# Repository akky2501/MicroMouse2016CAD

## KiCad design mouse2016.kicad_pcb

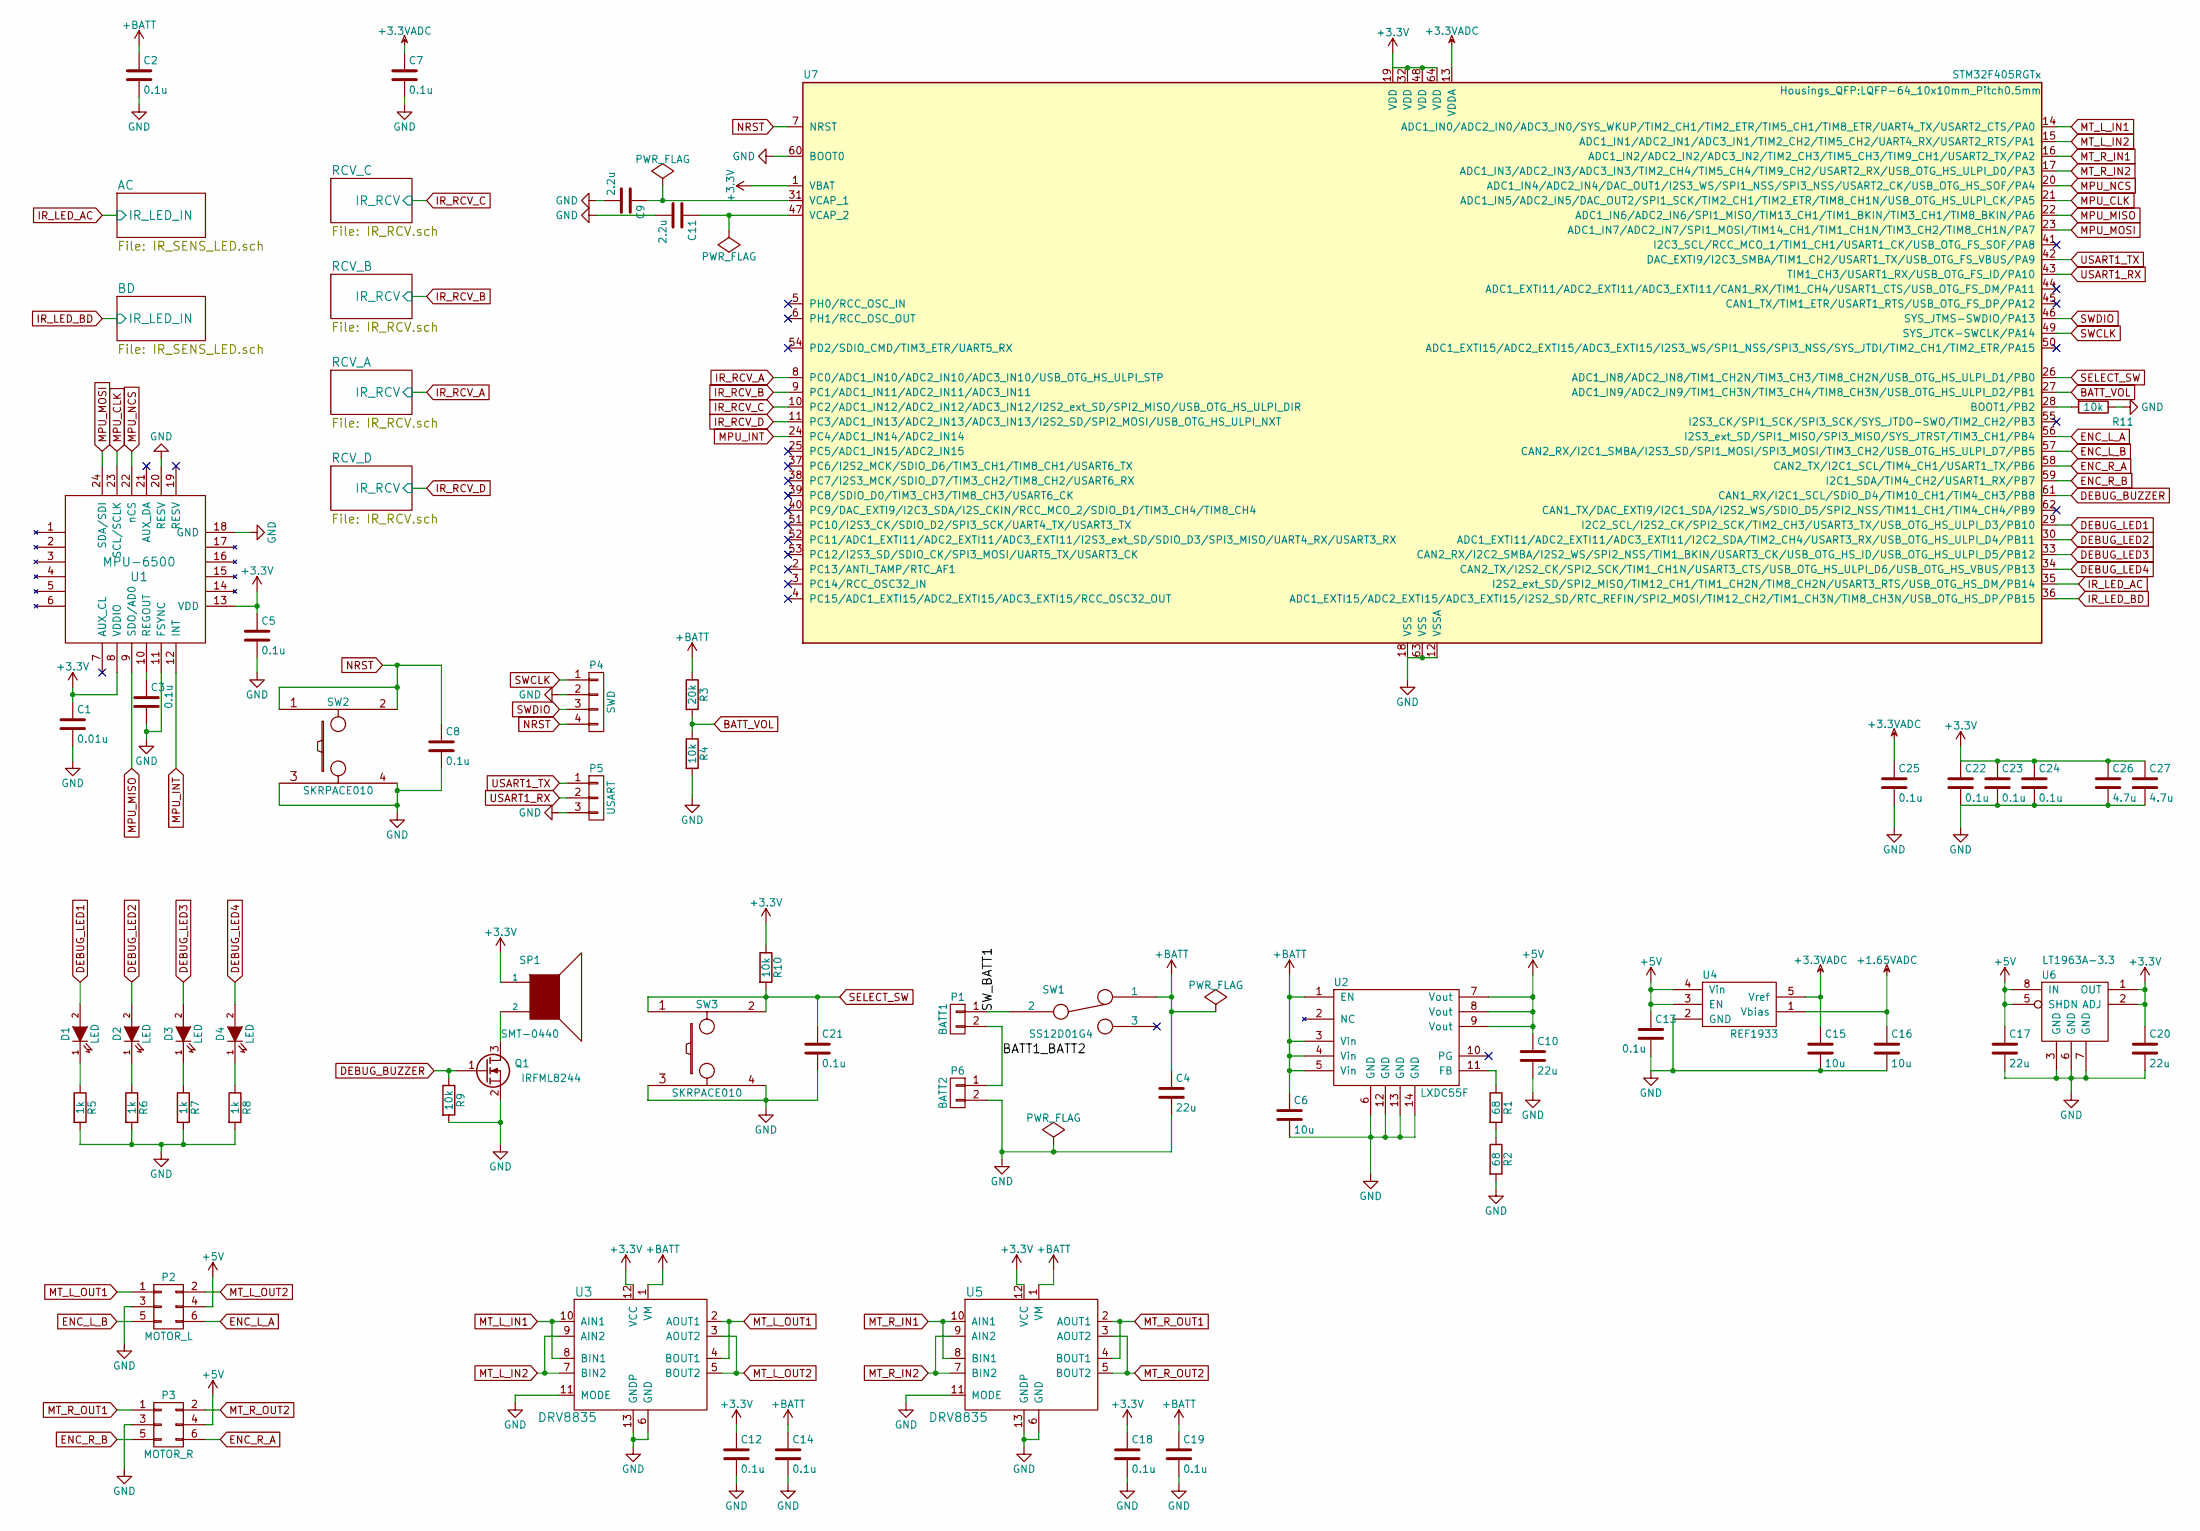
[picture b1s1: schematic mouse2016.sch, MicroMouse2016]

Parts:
C1: 0.01u; C_0603
C2, C3, C5, C7, C8, C12, C13, C14, C18, C19, C21, C22, C23, C24, C25: 0.1u; C_0603
C4, C10, C17, C20: 22u; C_0805
C6, C15, C16: 10u; C_0603
C9, C11: 2.2u; C_0603
C26, C27: 4.7u; C_0603
D1, D2, D3, D4: LED; LED_0603
P1: BATT1; JST_PH_B2B-PH-K_02x2.00mm_Straight
P2: MOTOR_L; Pin_Header_Straight_2x03
P3: MOTOR_R; Pin_Header_Straight_2x03
P4: SWD; JST_SH_BM04B-SRSS-TB_04x1.00mm_Straight
P5: USART; JST_SH_BM03B-SRSS-TB_03x1.00mm_Straight
P6: BATT2; JST_PH_B2B-PH-K_02x2.00mm_Straight
Q1: IRFML8244; SOT-23
R1, R2: 68; R_0603
R3: 20k; R_0603
R4, R9, R10, R11: 10k; R_0603
R5, R6, R7, R8: 1k; R_0603
SP1: SMT-0440; SMT-0440-S-R
SW1: SS12D01G4; SW_Micro_SPST
SW2, SW3: SKRPACE010
U1: MPU-6500; QFN-24-MPU6500
U2: LXDC55F; LXDC55FAAA-203_hole
U3, U5: DRV8835
U4: REF1933; SOT-23-5
U6: LT1963A-3.3; SOIC-8_3.9x4.9mm_Pitch1.27mm
U7: STM32F405RGTx; LQFP-64_10x10mm_Pitch0.5mm

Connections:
+1.65VADC: C16.1, U4.1 (Vbias); also elsewhere on the board
+3.3VADC: C7.1, C15.1, C25.1, U4.5 (Vref), U7.13 (VDDA); also elsewhere on the board
+3V3: C1.1, C5.1, C12.1, C18.1, C20.1, C22.1, C23.1, C24.1, C26.1, C27.1, R10.1, SP1.1, U1.8 (VDDIO), U1.13 (VDD), U3.12 (VCC), U5.12 (VCC), U6.1 (OUT), U6.2 (ADJ), U7.1 (VBAT), U7.19 (VDD), U7.32 (VDD), U7.48 (VDD), U7.64 (VDD)
+5V: C10.1, C13.1, C17.1, P2.4, P3.4, U2.7 (Vout), U2.8 (Vout), U2.9 (Vout), U4.3 (EN), U4.4 (Vin), U6.5 (SHDN), U6.8 (IN)
+BATT: C2.1, C4.1, C6.1, C14.1, C19.1, R3.1, SW1.1, U2.1 (EN), U2.3 (Vin), U2.4 (Vin), U2.5 (Vin), U3.1 (VM), U5.1 (VM); also elsewhere on the board
/BATT1_BATT2: P1.2, P6.1
/SW_BATT1: P1.1, SW1.2
BATT_VOL: R3.2, R4.1, U7.27 (ADC1_IN9/ADC2_IN9/TIM1_CH3N/TIM3_CH4/TI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)
DEBUG_BUZZER: Q1.1 (G), R9.1, U7.61 (CAN1_RX/I2C1_SCL/SDIO_D4/TIM10_CH1/TIM4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)
DEBUG_LED1: D1.2 (A), U7.29 (I2C2_SCL/I2S2_CK/SPI2_SCK/TIM2_CH3/USAR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)
DEBUG_LED2: D2.2 (A), U7.30 (ADC1_EXTI11/ADC2_EXTI11/ADC3_EXTI11/I2C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)
DEBUG_LED3: D3.2 (A), U7.33 (CAN2_RX/I2C2_SMBA/I2S2_WS/SPI2_NSS/TIM1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)
DEBUG_LED4: D4.2 (A), U7.34 (CAN2_TX/I2S2_CK/SPI2_SCK/TIM1_CH1N/USAR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)
ENC_L_A: P2.6, U7.56 (I2S3_ext_SD/SPI1_MISO/SPI3_MISO/SYS_JTR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)
ENC_L_B: P2.5, U7.57 (CAN2_RX/I2C1_SMBA/I2S3_SD/SPI1_MOSI/SPI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)
ENC_R_A: P3.6, U7.58 (CAN2_TX/I2C1_SCL/TIM4_CH1/USART1_TX/PB6)
ENC_R_B: P3.5, U7.59 (I2C1_SDA/TIM4_CH2/USART1_RX/PB7)
GND: C1.2, C2.2, C3.2, C4.2, C5.2, C6.2, C7.2, C8.2, C9.2, C10.2, C11.2, C12.2, C13.2, C14.2, C15.2, C16.2, C17.2, C18.2, C19.2, C20.2, C21.2, C22.2, C23.2, C24.2, C25.2, C26.2, C27.2, P2.3, P3.3, P4.2, P5.3, P6.2, Q1.2 (S), R2.2, R4.2, R5.2, R6.2, R7.2, R8.2, R9.2, R11.1, SW2.3, SW2.4, SW3.3, SW3.4, U1.11 (FSYNC), U1.18 (GND), U1.20 (RESV), U2.6 (GND), U2.12 (GND), U2.13 (GND), U2.14 (GND), U3.6 (GND), U3.11 (MODE), U3.13 (GNDP), U4.2 (GND), U5.6 (GND), U5.11 (MODE), U5.13 (GNDP), U6.3 (GND), U6.6 (GND), U6.7 (GND), U7.12 (VSSA), U7.18 (VSS), U7.60 (BOOT0), U7.63 (VSS); also elsewhere on the board
IR_LED_AC: U7.35 (I2S2_ext_SD/SPI2_MISO/TIM12_CH1/TIM1_CH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); also elsewhere on the board
IR_LED_BD: U7.36 (ADC1_EXTI15/ADC2_EXTI15/ADC3_EXTI15/I2S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); also elsewhere on the board
IR_RCV_A: U7.8 (PC0/ADC1_IN10/ADC2_IN10/ADC3_IN10/USB_O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); also elsewhere on the board
IR_RCV_B: U7.9 (PC1/ADC1_IN11/ADC2_IN11/ADC3_IN11); also elsewhere on the board
IR_RCV_C: U7.10 (PC2/ADC1_IN12/ADC2_IN12/ADC3_IN12/I2S2_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); also elsewhere on the board
IR_RCV_D: U7.11 (PC3/ADC1_IN13/ADC2_IN13/ADC3_IN13/I2S2_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); also elsewhere on the board
MPU_CLK: U1.23 (SCL/SCLK), U7.21 (ADC1_IN5/ADC2_IN5/DAC_OUT2/SPI1_SCK/TIM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)
MPU_INT: U1.12 (INT), U7.24 (PC4/ADC1_IN14/ADC2_IN14)
MPU_MISO: U1.9 (SDO/AD0), U7.22 (ADC1_IN6/ADC2_IN6/SPI1_MISO/TIM13_CH1/T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)
MPU_MOSI: U1.24 (SDA/SDI), U7.23 (ADC1_IN7/ADC2_IN7/SPI1_MOSI/TIM14_CH1/T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)
MPU_NCS: U1.22 (nCS), U7.20 (ADC1_IN4/ADC2_IN4/DAC_OUT1/I2S3_WS/SPI1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)
MT_L_IN1: U3.8 (BIN1), U3.10 (AIN1), U7.14 (ADC1_IN0/ADC2_IN0/ADC3_IN0/SYS_WKUP/TIM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)
MT_L_IN2: U3.7 (BIN2), U3.9 (AIN2), U7.15 (ADC1_IN1/ADC2_IN1/ADC3_IN1/TIM2_CH2/TIM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)
MT_L_OUT1: P2.1, U3.2 (AOUT1), U3.4 (BOUT1)
MT_L_OUT2: P2.2, U3.3 (AOUT2), U3.5 (BOUT2)
MT_R_IN1: U5.8 (BIN1), U5.10 (AIN1), U7.16 (ADC1_IN2/ADC2_IN2/ADC3_IN2/TIM2_CH3/TIM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)
MT_R_IN2: U5.7 (BIN2), U5.9 (AIN2), U7.17 (ADC1_IN3/ADC2_IN3/ADC3_IN3/TIM2_CH4/TIM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)
MT_R_OUT1: P3.1, U5.2 (AOUT1), U5.4 (BOUT1)
MT_R_OUT2: P3.2, U5.3 (AOUT2), U5.5 (BOUT2)
NRST: C8.1, P4.4, SW2.1, SW2.2, U7.7 (NRST)
unnamed: C3.1, U1.10 (REGOUT)
unnamed: C9.1, U7.31 (VCAP_1)
unnamed: C11.1, U7.47 (VCAP_2)
unnamed: D1.1 (K), R5.1
unnamed: D2.1 (K), R6.1
unnamed: D3.1 (K), R7.1
unnamed: D4.1 (K), R8.1
unnamed: Q1.3 (D), SP1.2
unnamed: R1.1, U2.11 (FB)
unnamed: R1.2, R2.1
unnamed: R11.2, U7.28 (BOOT1/PB2)
SELECT_SW: C21.1, R10.2, SW3.1, SW3.2, U7.26 (ADC1_IN8/ADC2_IN8/TIM1_CH2N/TIM3_CH3/TI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)
SWCLK: P4.1, U7.49 (SYS_JTCK-SWCLK/PA14)
SWDIO: P4.3, U7.46 (SYS_JTMS-SWDIO/PA13)
USART1_RX: P5.2, U7.43 (TIM1_CH3/USART1_RX/USB_OTG_FS_ID/PA10)
USART1_TX: P5.1, U7.42 (DAC_EXTI9/I2C3_SMBA/TIM1_CH2/USART1_TX/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)

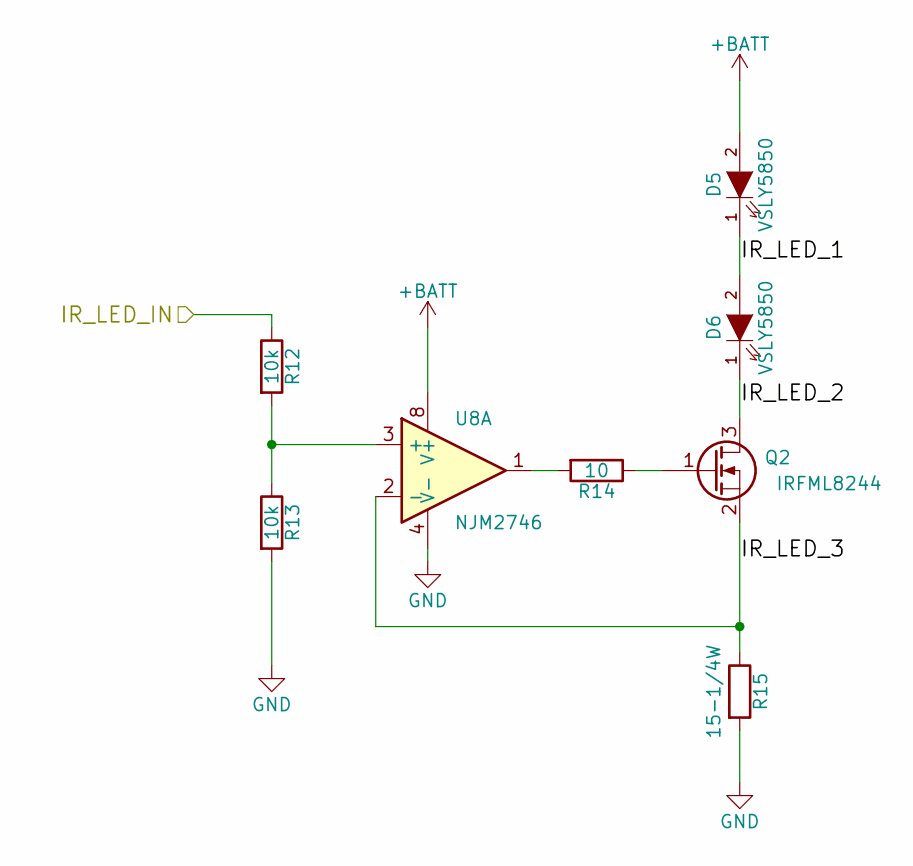
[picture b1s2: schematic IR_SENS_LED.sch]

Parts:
D5, D6: VSLY5850; LED
Q2: IRFML8244; SOT-23
R12, R13: 10k; R_0603
R14: 10; R_0603
R15: 15-1/4W; R_1206
U8: NJM2746; SOIC-8_3.9x4.9mm_Pitch1.27mm

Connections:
+BATT: D5.2 (A), U8.8 (V+); also elsewhere on the board
/AC/IR_LED_1: D5.1 (K), D6.2 (A)
/AC/IR_LED_2: D6.1 (K), Q2.3 (D)
/AC/IR_LED_3: Q2.2 (S), R15.1, U8.2 (-)
/BD/IR_LED_3: U8.6 (-); also elsewhere on the board
GND: R13.2, R15.2, U8.4 (V-); also elsewhere on the board
IR_LED_AC: R12.1; also elsewhere on the board
unnamed: Q2.1 (G), R14.1
unnamed: R12.2, R13.1, U8.3 (+)
unnamed: R14.2, U8.1
unnamed 67: U8.5 (+); also elsewhere on the board
unnamed 68: U8.7; also elsewhere on the board

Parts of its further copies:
D7, D8: VSLY5850; LED
Q3: IRFML8244; SOT-23
R16, R17: 10k; R_0603
R18: 10; R_0603
R19: 15-1/4W; R_1206

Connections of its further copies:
+BATT: D8.2 (A); also elsewhere on the board
/BD/IR_LED_1: D7.2 (A), D8.1 (K)
/BD/IR_LED_2: D7.1 (K), Q3.3 (D)
/BD/IR_LED_3: Q3.2 (S), R19.1; also elsewhere on the board
GND: R17.2, R19.2; also elsewhere on the board
IR_LED_BD: R16.1; also elsewhere on the board
unnamed: Q3.1 (G), R18.1
unnamed 67: R16.2, R17.1; also elsewhere on the board
unnamed 68: R18.2; also elsewhere on the board

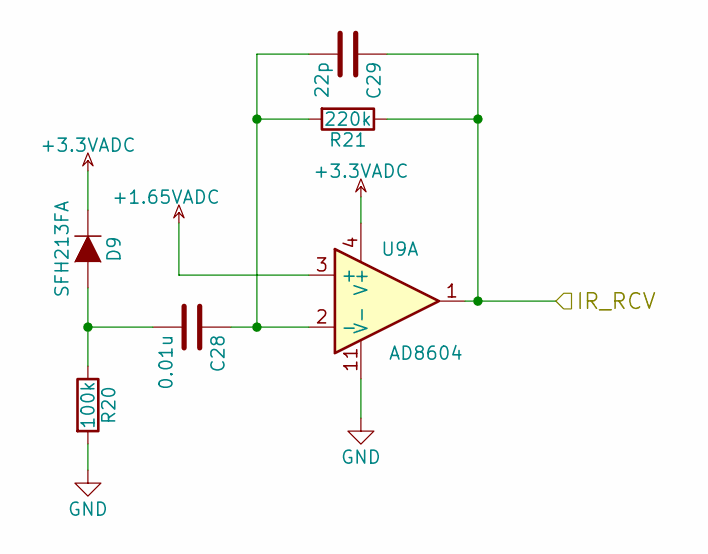
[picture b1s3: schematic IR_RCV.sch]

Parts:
C28: 0.01u; C_0603
C29: 22p; C_0603
D9: SFH213FA; LED
R20: 100k; R_0603
R21: 220k; R_0603
U9: AD8604; TSSOP-14_4.4x5mm_Pitch0.65mm

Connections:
+1.65VADC: U9.3 (+), U9.5 (+), U9.10 (+), U9.12 (+); also elsewhere on the board
+3.3VADC: D9.1 (K), U9.4 (V+); also elsewhere on the board
GND: R20.2, U9.11 (V-); also elsewhere on the board
IR_RCV_A: U9.8; also elsewhere on the board
IR_RCV_B: U9.7; also elsewhere on the board
IR_RCV_C: C29.1, R21.1, U9.1; also elsewhere on the board
IR_RCV_D: U9.14; also elsewhere on the board
unnamed: C28.1, C29.2, R21.2, U9.2 (-)
unnamed: C28.2, D9.2 (A), R20.1
unnamed 49: U9.6 (-); also elsewhere on the board
unnamed 51: U9.9 (-); also elsewhere on the board
unnamed 53: U9.13 (-); also elsewhere on the board

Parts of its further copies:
C30, C32, C34: 0.01u; C_0603
C31, C33, C35: 22p; C_0603
D10, D11, D12: SFH213FA; LED
R22, R24, R26: 100k; R_0603
R23, R25, R27: 220k; R_0603

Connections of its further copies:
+3.3VADC: D10.1 (K), D11.1 (K), D12.1 (K); also elsewhere on the board
GND: R22.2, R24.2, R26.2; also elsewhere on the board
IR_RCV_A: C33.1, R25.1; also elsewhere on the board
IR_RCV_B: C31.1, R23.1; also elsewhere on the board
IR_RCV_D: C35.1, R27.1; also elsewhere on the board
unnamed 49: C30.1, C31.2, R23.2; also elsewhere on the board
unnamed: C30.2, D10.2 (A), R22.1
unnamed 51: C32.1, C33.2, R25.2; also elsewhere on the board
unnamed: C32.2, D11.2 (A), R24.1
unnamed 53: C34.1, C35.2, R27.2; also elsewhere on the board
unnamed: C34.2, D12.2 (A), R26.1

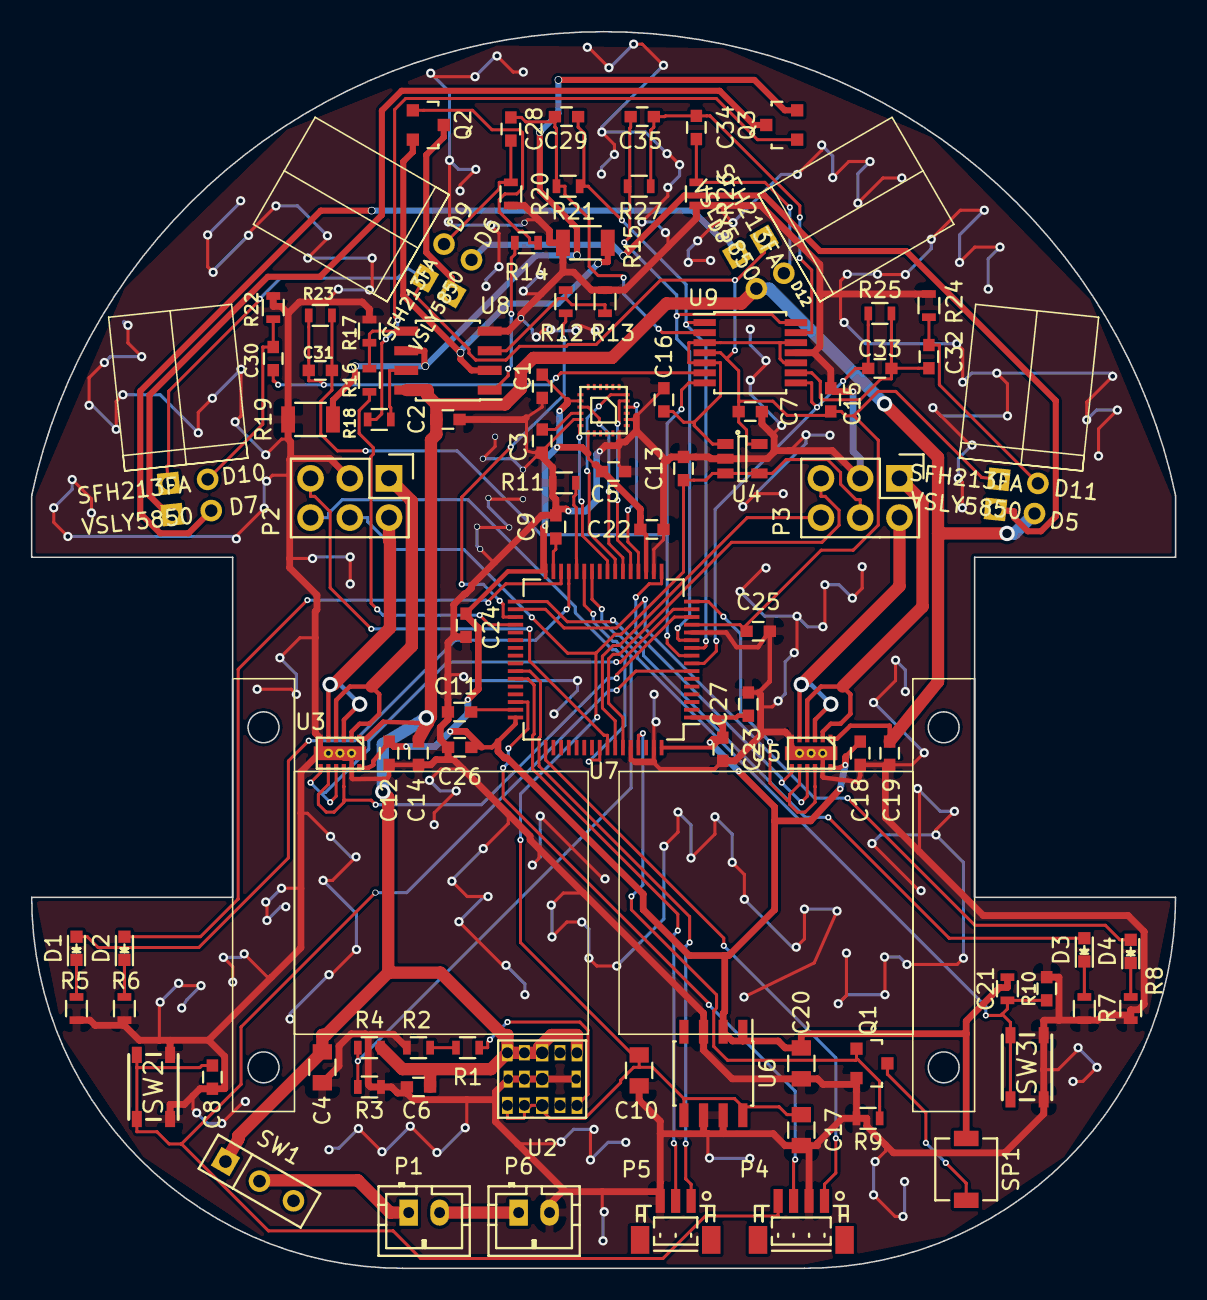
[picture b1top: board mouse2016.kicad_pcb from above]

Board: 2 copper layers, 74.0 x 80.0 mm, 96 parts (0 on the bottom side), 74 nets.

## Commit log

2017-05-29 second commit
